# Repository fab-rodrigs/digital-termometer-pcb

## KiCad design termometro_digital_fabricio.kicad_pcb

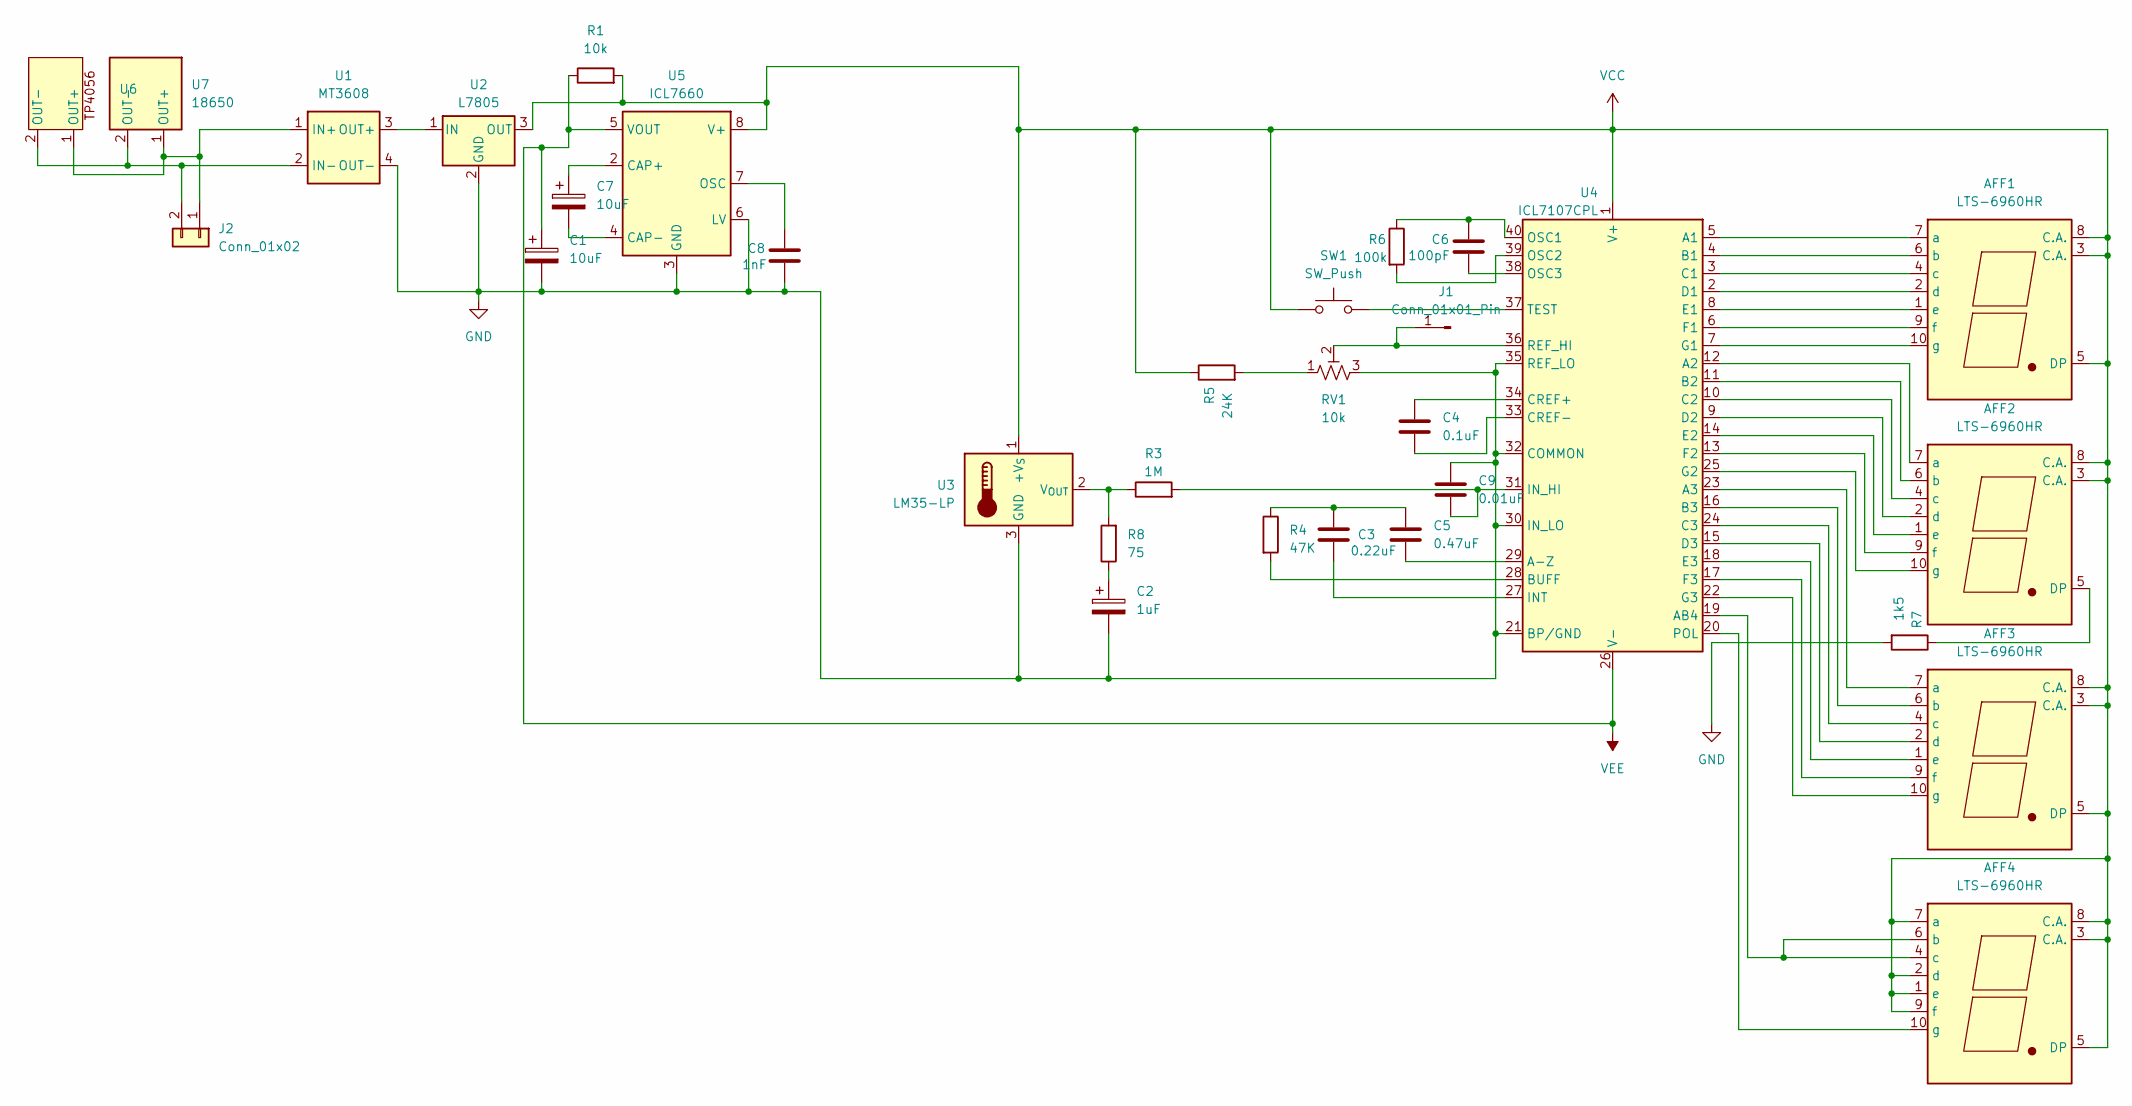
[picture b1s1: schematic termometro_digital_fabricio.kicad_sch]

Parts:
AFF1, AFF2, AFF3, AFF4: LTS-6960HR; 7SegmentLED_LTS6760_LTS6780
C1, C7: 10uF; CP_Radial_D5.0mm_P2.00mm
C2: 1uF; CP_Radial_D4.0mm_P1.50mm
C3: 0.22uF; C_Disc_D10.5mm_W5.0mm_P7.50mm
C4: 0.1uF; C_Disc_D10.5mm_W5.0mm_P7.50mm
C5: 0.47uF; C_Disc_D12.5mm_W5.0mm_P10.00mm
C6: 100pF; C_Disc_D10.5mm_W5.0mm_P5.00mm
C8: 1nF; C_Disc_D10.5mm_W5.0mm_P5.00mm
C9: 0.01uF; C_Disc_D10.5mm_W5.0mm_P7.50mm
J1: Conn_01x01_Pin; PinHeader_1x01_P1.00mm_Vertical
J2: Conn_01x02; TerminalBlock_Phoenix_MKDS-1,5-2-5.08_1x02_P5.08mm_Horizont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
R1: 10k; R_Axial_DIN0309_L9.0mm_D3.2mm_P15.24mm_Horizontal
R3: 1M; R_Axial_DIN0309_L9.0mm_D3.2mm_P15.24mm_Horizontal
R4: 47K; R_Axial_DIN0309_L9.0mm_D3.2mm_P15.24mm_Horizontal
R5: 24K; R_Axial_DIN0309_L9.0mm_D3.2mm_P15.24mm_Horizontal
R6: 100k; R_Axial_DIN0309_L9.0mm_D3.2mm_P15.24mm_Horizontal
R7: 1k5; R_Axial_DIN0309_L9.0mm_D3.2mm_P15.24mm_Horizontal
R8: 75; R_Axial_DIN0309_L9.0mm_D3.2mm_P15.24mm_Horizontal
RV1: 10k; TRIM_3296W-1-250
SW1: SW_Push; SW_PUSH_6mm
U1: MT3608
U2: L7805; TO-220-3_Vertical
U3: LM35-LP; TO-92_Inline_Wide
U4: ICL7107CPL; DIP-40_W15.24mm_LongPads
U5: ICL7660; DIP-8_W7.62mm_LongPads
U6: TP4056
U7: 18650; SOT-23-6

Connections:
GND: C1.2, C2.2, C8.2, C9.1, R7.2, RV1.3, U1.4 (OUT-), U2.2 (GND), U3.3 (GND), U4.21 (BP/GND), U4.30 (IN_LO), U4.32 (COMMON), U4.35 (REF_LO), U5.3 (GND), U5.6 (LV)
unnamed: AFF1.7 (a), U4.5 (A1)
unnamed: AFF1.6 (b), U4.4 (B1)
unnamed: AFF1.4 (c), U4.3 (C1)
unnamed: AFF1.2 (d), U4.2 (D1)
unnamed: AFF1.1 (e), U4.8 (E1)
unnamed: AFF1.9 (f), U4.6 (F1)
unnamed: AFF1.10 (g), U4.7 (G1)
unnamed: AFF2.5 (DP), R7.1
unnamed: AFF2.7 (a), U4.12 (A2)
unnamed: AFF2.6 (b), U4.11 (B2)
unnamed: AFF2.4 (c), U4.10 (C2)
unnamed: AFF2.2 (d), U4.9 (D2)
unnamed: AFF2.1 (e), U4.14 (E2)
unnamed: AFF2.9 (f), U4.13 (F2)
unnamed: AFF2.10 (g), U4.25 (G2)
unnamed: AFF3.7 (a), U4.23 (A3)
unnamed: AFF3.6 (b), U4.16 (B3)
unnamed: AFF3.4 (c), U4.24 (C3)
unnamed: AFF3.2 (d), U4.15 (D3)
unnamed: AFF3.1 (e), U4.18 (E3)
unnamed: AFF3.9 (f), U4.17 (F3)
unnamed: AFF3.10 (g), U4.22 (G3)
unnamed: AFF4.4 (c), AFF4.6 (b), U4.19 (AB4)
unnamed: AFF4.10 (g), U4.20 (POL)
unnamed: C2.1, R8.1
unnamed: C3.1, C5.1, R4.1
unnamed: J1.1, RV1.2, U4.36 (REF_HI)
unnamed: R5.2, RV1.1
unnamed: U1.3 (OUT+), U2.1 (IN)
unnamed: R3.1, R8.2, U3.2 (V_{OUT})
unnamed: C5.2, U4.29 (A-Z)
unnamed: R4.2, U4.28 (BUFF)
unnamed: C4.1, U4.34 (CREF+)
unnamed: C4.2, U4.33 (CREF-)
unnamed: C3.2, U4.27 (INT)
unnamed: C9.2, R3.2, U4.31 (IN_HI)
unnamed: C6.1, R6.1, U4.40 (OSC1)
unnamed: R6.2, U4.39 (OSC2)
unnamed: C6.2, U4.38 (OSC3)
unnamed: SW1.2, U4.37 (TEST)
unnamed: C7.1, U5.2 (CAP+)
unnamed: C7.2, U5.4 (CAP-)
unnamed: C8.1, U5.7 (OSC)
VCC: AFF1.3 (C.A.), AFF1.5 (DP), AFF1.8 (C.A.), AFF2.3 (C.A.), AFF2.8 (C.A.), AFF3.3 (C.A.), AFF3.5 (DP), AFF3.8 (C.A.), AFF4.1 (e), AFF4.2 (d), AFF4.3 (C.A.), AFF4.5 (DP), AFF4.7 (a), AFF4.8 (C.A.), AFF4.9 (f), R1.2, R5.1, SW1.1, U2.3 (OUT), U3.1 (+V_{S}), U4.1 (V+), U5.8 (V+)
VEE: C1.1, R1.1, U4.26 (V-), U5.5 (VOUT)

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
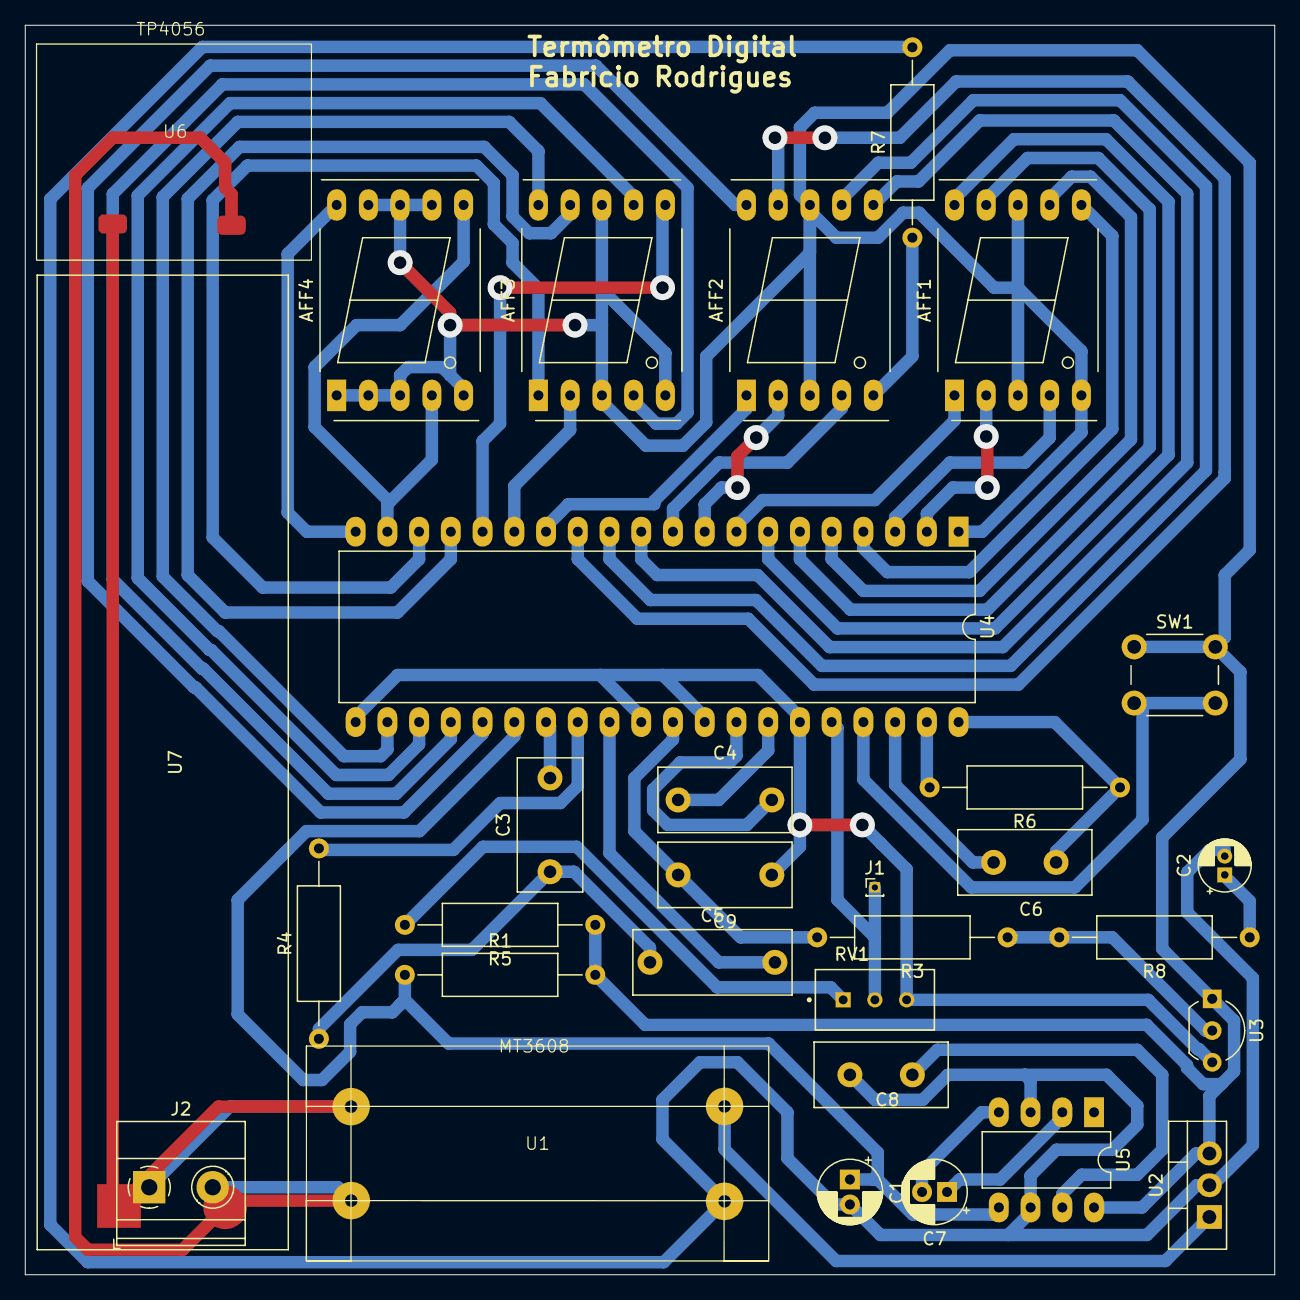
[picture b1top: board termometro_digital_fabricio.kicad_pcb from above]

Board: 2 copper layers, 100.0 x 100.0 mm, 31 parts (0 on the bottom side), 48 nets.

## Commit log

2025-07-18 Uploading files
